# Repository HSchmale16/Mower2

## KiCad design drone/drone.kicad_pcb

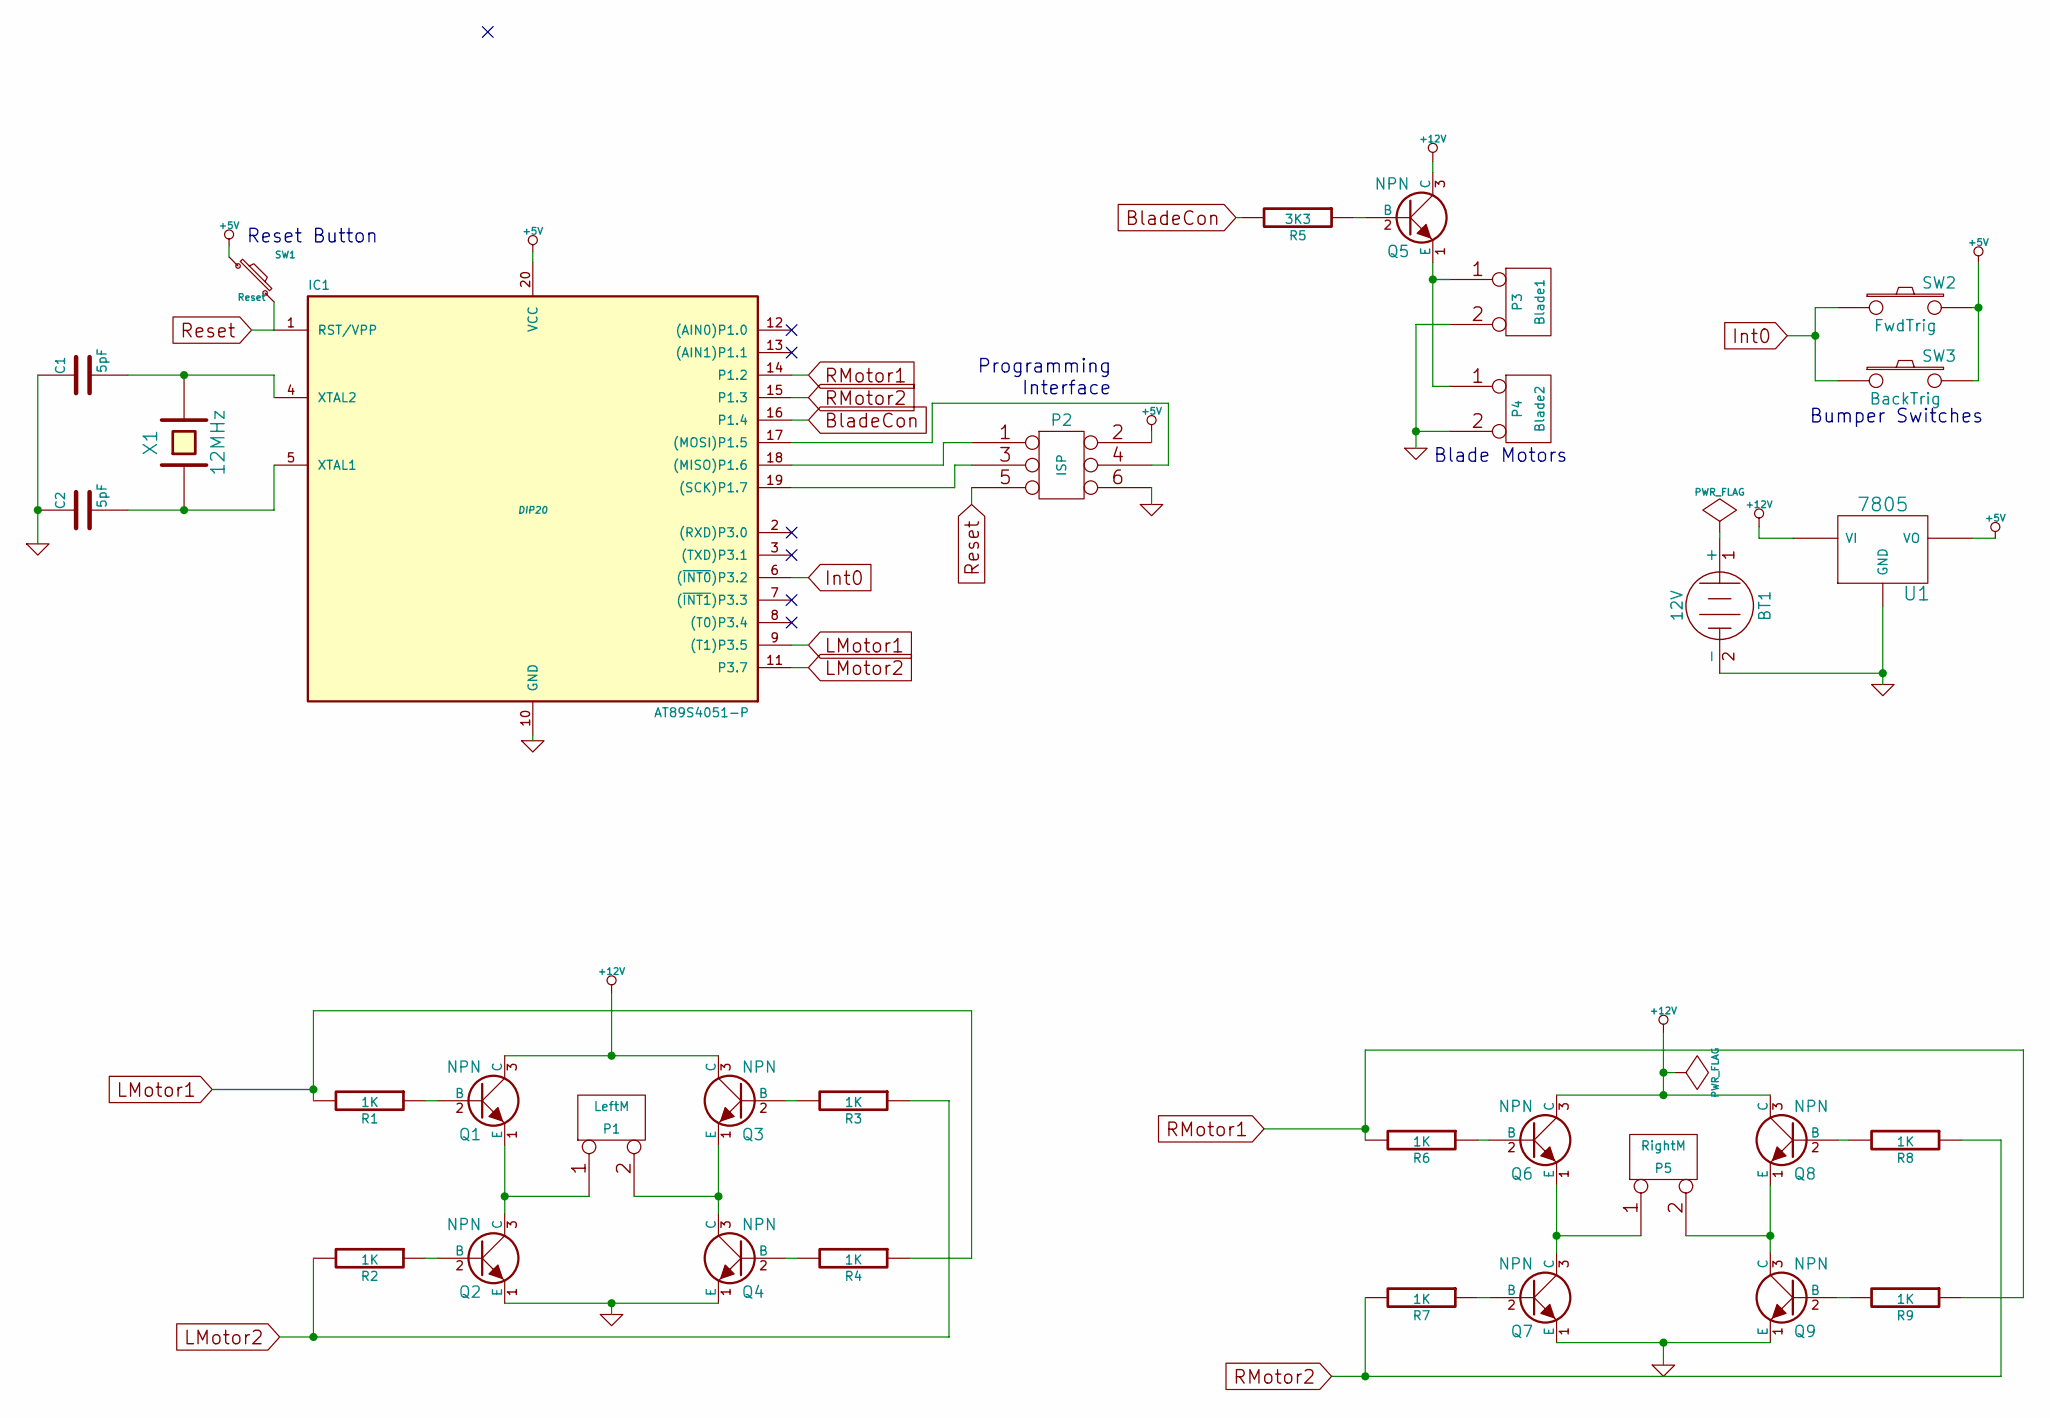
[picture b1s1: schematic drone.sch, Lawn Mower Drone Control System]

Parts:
BT1: 12V
C1, C2: 5pF
IC1: AT89S4051-P; DIP20
P1: LeftM
P2: ISP
P3: Blade1
P4: Blade2
P5: RightM
Q1, Q2, Q3, Q4, Q5, Q6, Q7, Q8, Q9: NPN
R1, R2, R3, R4, R6, R7, R8, R9: 1K
R5: 3K3
SW1: Reset
SW2: FwdTrig
SW3: BackTrig
U1: 7805
X1: 12MHz

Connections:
+5V: IC1.20 (VCC), P2.2, SW1.1, SW2.2, SW3.2, U1.VO
+12V: Q1.3 (C), Q3.3 (C), Q5.3 (C), Q6.3 (C), Q8.3 (C), U1.VI
BladeCon: IC1.16 (P1.4), R5.2
GND: BT1.2 (-), C1.1, C2.1, IC1.10 (GND), P2.6, P3.2 (PM), P4.2 (PM), Q2.1 (E), Q4.1 (E), Q7.1 (E), Q9.1 (E), U1.GND
Int0: IC1.6 ((~INT0~)P3.2), SW2.1, SW3.1
LMotor1: IC1.9 ((T1)P3.5), R1.2, R4.1
LMotor2: IC1.11 (P3.7), R2.2, R3.1
unnamed: C1.2, IC1.4 (XTAL2), X1.2
unnamed: C2.2, IC1.5 (XTAL1), X1.1
unnamed: IC1.17 ((MOSI)P1.5), P2.4
unnamed: IC1.18 ((MISO)P1.6), P2.1
unnamed: IC1.19 ((SCK)P1.7), P2.3
unnamed: P1.1, Q1.1 (E), Q2.3 (C)
unnamed: P1.2 (PM), Q3.1 (E), Q4.3 (C)
unnamed: P3.1, P4.1, Q5.1 (E)
unnamed: P5.1, Q6.1 (E), Q7.3 (C)
unnamed: P5.2 (PM), Q8.1 (E), Q9.3 (C)
unnamed: Q1.2 (B), R1.1
unnamed: Q2.2 (B), R2.1
unnamed: Q3.2 (B), R3.2
unnamed: Q4.2 (B), R4.2
unnamed: Q5.2 (B), R5.1
unnamed: Q6.2 (B), R6.1
unnamed: Q7.2 (B), R7.1
unnamed: Q8.2 (B), R8.2
unnamed: Q9.2 (B), R9.2
RMotor1: IC1.14 (P1.2), R6.2, R9.1
RMotor2: IC1.15 (P1.3), R7.2, R8.1
Reset: IC1.1 (RST/VPP), P2.5, SW1.2

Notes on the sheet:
Reset Button
Programming Interface
Bumper Switches
Blade Motors

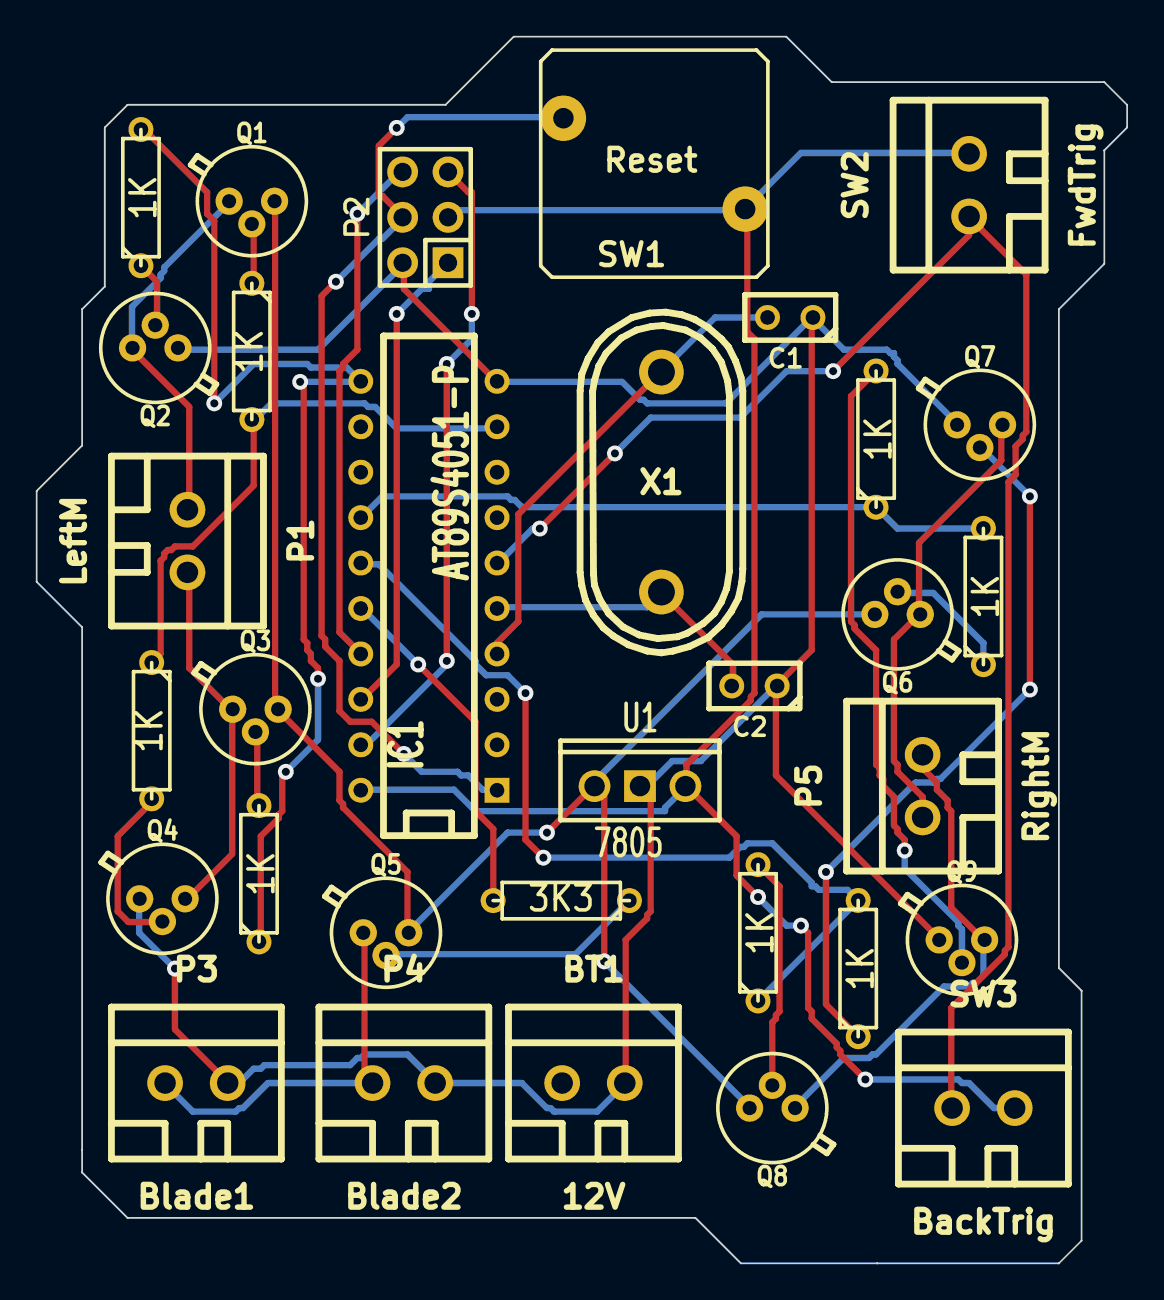
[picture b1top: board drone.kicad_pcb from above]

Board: 2 copper layers, 61.0 x 68.6 mm, 32 parts (0 on the bottom side), 29 nets.

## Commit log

2015-06-01 Drone Schematics Initial Commit
2015-06-01 Schematic
2015-06-01 Worked on the drone
    * Added the assembly files
2015-06-02 Worked on the drone schematic
    * Wrote some code
    * Setup interupts for the controller
    * Wrote basic framework of code
    * Worked on the schematic
    * Placed parts
    * Made notes
2015-06-02 Worked on the project some more
    * Added L293NE to schematic lib
    * Drew some more of the schematic
2015-06-02 Worked on the mower drone
    * Drew more of the schematic
    * Worked on the assmebly program
2015-06-03 Worked on the drone
2015-06-03 Added netlist
    * Added the netlist
    * Worked on the schematic
2015-06-03 Worked on the drone schematic
    * It is really difficult to get relays that are cheap as such
    the motor control was switched using an H-Bridge Configuration
    to control motor state and direction
    * Added a bunch of symbols to the cache library.
    * Relays and lots of them.
    * Started work on the netlist
2015-06-03 Associated parts in the netlist
2015-06-03 Layed out the pcb
    * The pcb is on version 0.1
2015-06-04 Revised the PCB design
    * Set the board outlines
    * Worked on the message text
2015-06-04 Layed out the board completely
2015-06-04 Updated the board layout
2015-06-04 Worked on the assembly program
    * Worked on the assembly program
    * Worked on the schmatic
    * Issue Date
    * Notes
2015-06-04 Fix the circuit
2015-06-04 Fixed design rules check fail
    * It just needed such a pwr-flag on the power and ground networks
2015-06-05 Wrote a real wait function
    * Wrote a wait sub that waits for timer0 to overflow R0
    * Rerouted the Pcb
2015-06-07 Worked on the assembly
2015-06-08 Added ultrasonic range finder to schematic
    * Added an ultra sonic rangefinder to schematic
    Avail Here: http://www.amazon.com/SunFounder-Ultrasonic-Distance-Mega2560-Duemilanove/dp/B00E0NXTJW/ref=sr_1_1?ie=UTF8&qid=1433724748&sr=8-1&keywords=Ultrasonic+arduino
2015-06-08 Moved echo pin to interupt 1
    * Interupt 1 is better for range finding
2015-06-08 Worked on the asmbly prog
    * Started working on the range finder
    * Documented program a bit
    * Edited the schematic so that it is better
2015-06-08 Worked some more
2015-06-09 Edited Schematic
2015-06-09 Worked on the assembly code
    * Added a good range finder subroutine from http://www.circuitstoday.com/ultrasonic-range-finder-using-8051
2015-06-09 Worked on the assembly even more
